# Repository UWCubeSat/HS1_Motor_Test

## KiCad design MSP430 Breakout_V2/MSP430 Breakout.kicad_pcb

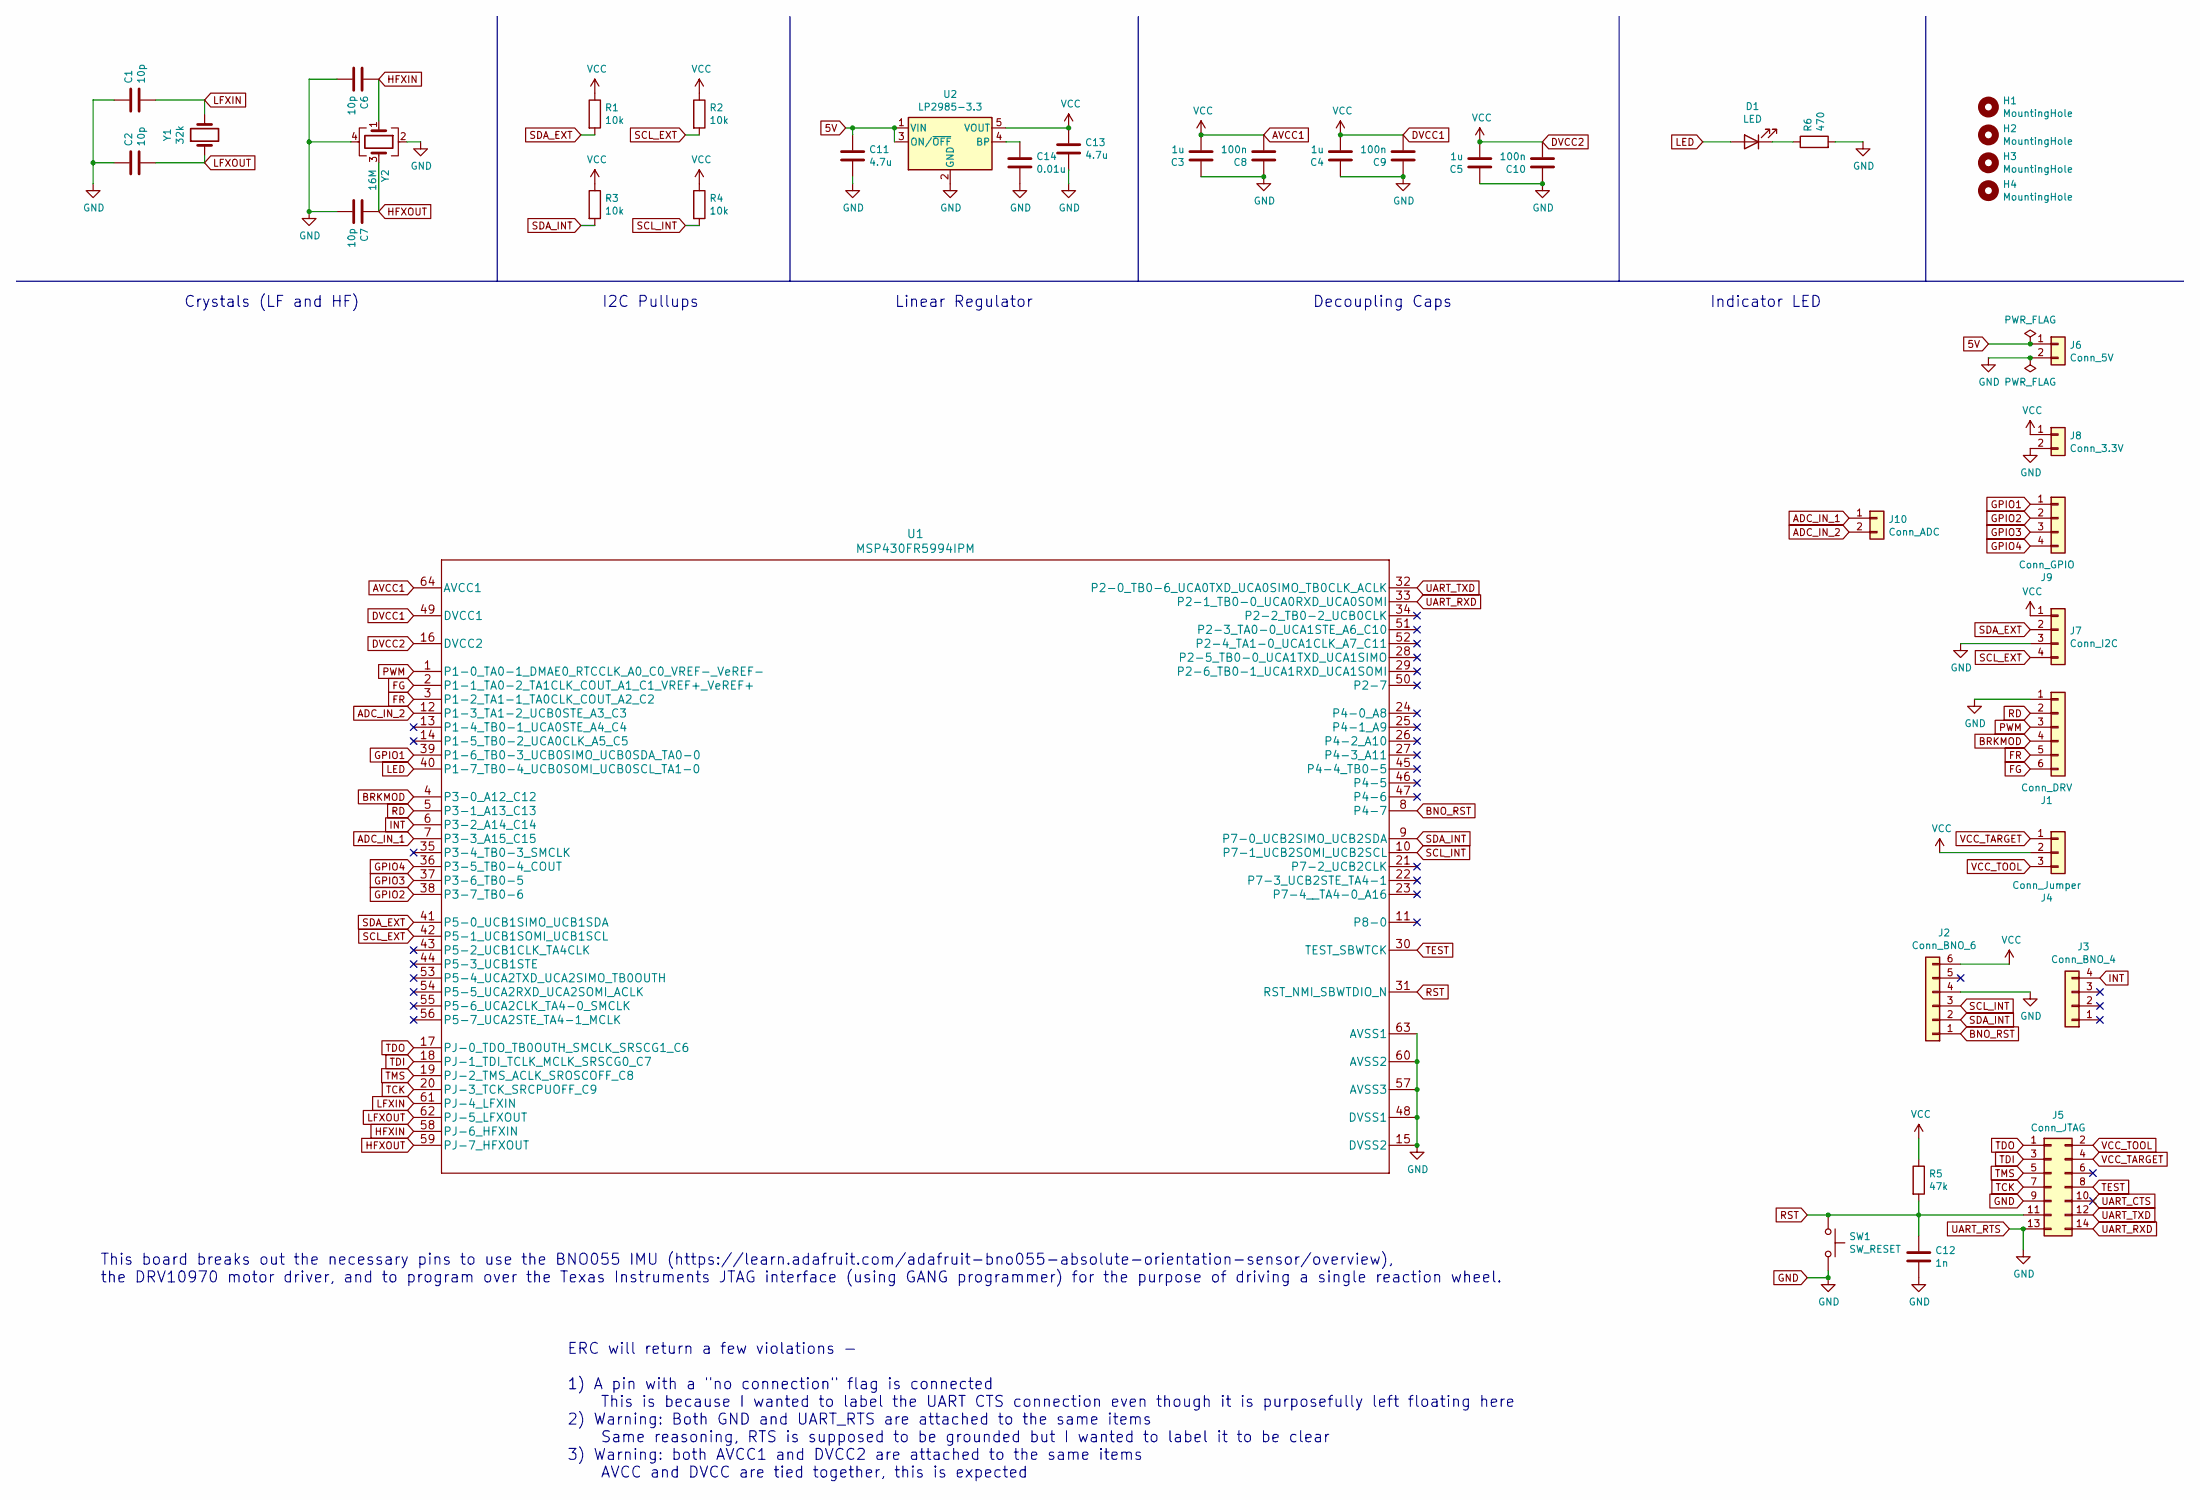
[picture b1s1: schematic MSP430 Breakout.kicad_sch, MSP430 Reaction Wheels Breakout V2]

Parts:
C1, C2, C6, C7: 10p; C_0805_2012Metric_Pad1.18x1.45mm_HandSolder
C3, C4, C5: 1u; C_0805_2012Metric_Pad1.18x1.45mm_HandSolder
C8, C9, C10: 100n; C_0805_2012Metric_Pad1.18x1.45mm_HandSolder
C11, C13: 4.7u; C_0805_2012Metric_Pad1.18x1.45mm_HandSolder
C12: 1n; C_0805_2012Metric_Pad1.18x1.45mm_HandSolder
C14: 0.01u; C_0805_2012Metric_Pad1.18x1.45mm_HandSolder
D1: LED; LED_0805_2012Metric_Pad1.15x1.40mm_HandSolder
H1, H2, H3, H4: MountingHole; MountingHole_2.5mm_Pad_Via
J1: Conn_DRV; PinSocket_1x06_P2.54mm_Vertical
J2: Conn_BNO_6; PinSocket_1x06_P2.54mm_Vertical
J3: Conn_BNO_4; PinSocket_1x04_P2.54mm_Vertical
J4: Conn_Jumper; PinHeader_1x03_P2.54mm_Vertical
J5: Conn_JTAG; PinHeader_2x07_P2.54mm_Vertical
J6: Conn_5V; PinSocket_1x02_P2.54mm_Vertical
J7: Conn_I2C; PinSocket_1x04_P2.54mm_Vertical
J8: Conn_3.3V; PinSocket_1x02_P2.54mm_Vertical
J9: Conn_GPIO; PinSocket_1x04_P2.54mm_Vertical
J10: Conn_ADC; PinSocket_1x02_P2.54mm_Vertical
R1, R2, R3, R4: 10k; R_0805_2012Metric_Pad1.20x1.40mm_HandSolder
R5: 47k; R_0805_2012Metric_Pad1.20x1.40mm_HandSolder
R6: 470; R_0805_2012Metric_Pad1.20x1.40mm_HandSolder
SW1: SW_RESET; SW_PUSH_6mm_H5mm
U1: MSP430FR5994IPM
U2: LP2985-3.3; SOT-23-5
Y1: 32k; Crystal_SMD_2012-2Pin_2.0x1.2mm
Y2: 16M; Crystal_SMD_3225-4Pin_3.2x2.5mm_HandSoldering

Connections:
5V: C11.1, J6.1, U2.1 (VIN), U2.3 (ON/~OFF)
ADC_IN_1: J10.1, U1.7 (P3-3_A15_C15)
ADC_IN_2: J10.2, U1.12 (P1-3_TA1-2_UCB0STE_A3_C3)
AVCC1: C3.2, C4.2, C5.2, C8.2, C9.2, C10.2, C13.1, J2.6, J4.2, J7.1, J8.1, R1.1, R2.1, R3.1, R4.1, R5.1, U1.16 (DVCC2), U1.49 (DVCC1), U1.64 (AVCC1), U2.5 (VOUT)
BNO_RST: J2.1, U1.8 (P4-7)
BRKMOD: J1.4, U1.4 (P3-0_A12_C12)
FG: J1.6, U1.2 (P1-1_TA0-2_TA1CLK_COUT_A1_C1_VREF+_VeRE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)
FR: J1.5, U1.3 (P1-2_TA1-1_TA0CLK_COUT_A2_C2)
GND: C1.1, C2.1, C3.1, C4.1, C5.1, C6.2, C7.2, C8.1, C9.1, C10.1, C11.2, C12.2, C13.2, C14.2, J1.1, J2.4, J5.9, J5.13, J6.2, J7.3, J8.2, R6.2, SW1.2, U1.15 (DVSS2), U1.48 (DVSS1), U1.57 (AVSS3), U1.60 (AVSS2), U1.63 (AVSS1), U2.2 (GND), Y2.2, Y2.4
GPIO1: J9.1, U1.39 (P1-6_TB0-3_UCB0SIMO_UCB0SDA_TA0-0)
GPIO2: J9.2, U1.38 (P3-7_TB0-6)
GPIO3: J9.3, U1.37 (P3-6_TB0-5)
GPIO4: J9.4, U1.36 (P3-5_TB0-4_COUT)
HFXIN: C6.1, U1.58 (PJ-6_HFXIN), Y2.1
HFXOUT: C7.1, U1.59 (PJ-7_HFXOUT), Y2.3
INT: J3.4, U1.6 (P3-2_A14_C14)
LED: D1.2 (A), U1.40 (P1-7_TB0-4_UCB0SOMI_UCB0SCL_TA1-0)
LFXIN: C1.2, U1.61 (PJ-4_LFXIN), Y1.2
LFXOUT: C2.2, U1.62 (PJ-5_LFXOUT), Y1.1
unnamed: C14.1, U2.4 (BP)
unnamed: D1.1 (K), R6.1
PWM: J1.3, U1.1 (P1-0_TA0-1_DMAE0_RTCCLK_A0_C0_VREF-_VeR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)
RD: J1.2, U1.5 (P3-1_A13_C13)
RST: C12.1, J5.11, R5.2, SW1.1, U1.31 (RST_NMI_SBWTDIO_N)
SCL_EXT: J7.4, R2.2, U1.42 (P5-1_UCB1SOMI_UCB1SCL)
SCL_INT: J2.3, R4.2, U1.10 (P7-1_UCB2SOMI_UCB2SCL)
SDA_EXT: J7.2, R1.2, U1.41 (P5-0_UCB1SIMO_UCB1SDA)
SDA_INT: J2.2, R3.2, U1.9 (P7-0_UCB2SIMO_UCB2SDA)
TCK: J5.7, U1.20 (PJ-3_TCK_SRCPUOFF_C9)
TDI: J5.3, U1.18 (PJ-1_TDI_TCLK_MCLK_SRSCG0_C7)
TDO: J5.1, U1.17 (PJ-0_TDO_TB0OUTH_SMCLK_SRSCG1_C6)
TEST: J5.8, U1.30 (TEST_SBWTCK)
TMS: J5.5, U1.19 (PJ-2_TMS_ACLK_SROSCOFF_C8)
UART_CTS: J5.10
UART_RXD: J5.14, U1.33 (P2-1_TB0-0_UCA0RXD_UCA0SOMI)
UART_TXD: J5.12, U1.32 (P2-0_TB0-6_UCA0TXD_UCA0SIMO_TB0CLK_ACLK)
VCC_TARGET: J4.1, J5.4
VCC_TOOL: J4.3, J5.2

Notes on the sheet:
I2C Pullups
This board breaks out the necessary pins to use the BNO055 IMU (https://learn.adafruit.com/adafruit-bno055-absolute-orientation-sensor/overview), the DRV10970 motor driver, and to program over the Texas Instruments JTAG interface (using GANG programmer) for the purpose of driving a single reaction 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
ERC will return a few violations - 1) A pin with a "no connection" flag is connected This is because I wanted to label the UART CTS connection even though it is purposefully left floating here 2) Warning: Both GND and UART_RTS are attached to the same items Same reasoning, RTS is supposed to be gro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
Linear Regulator
Decoupling Caps
Crystals (LF and HF)
Indicator LED

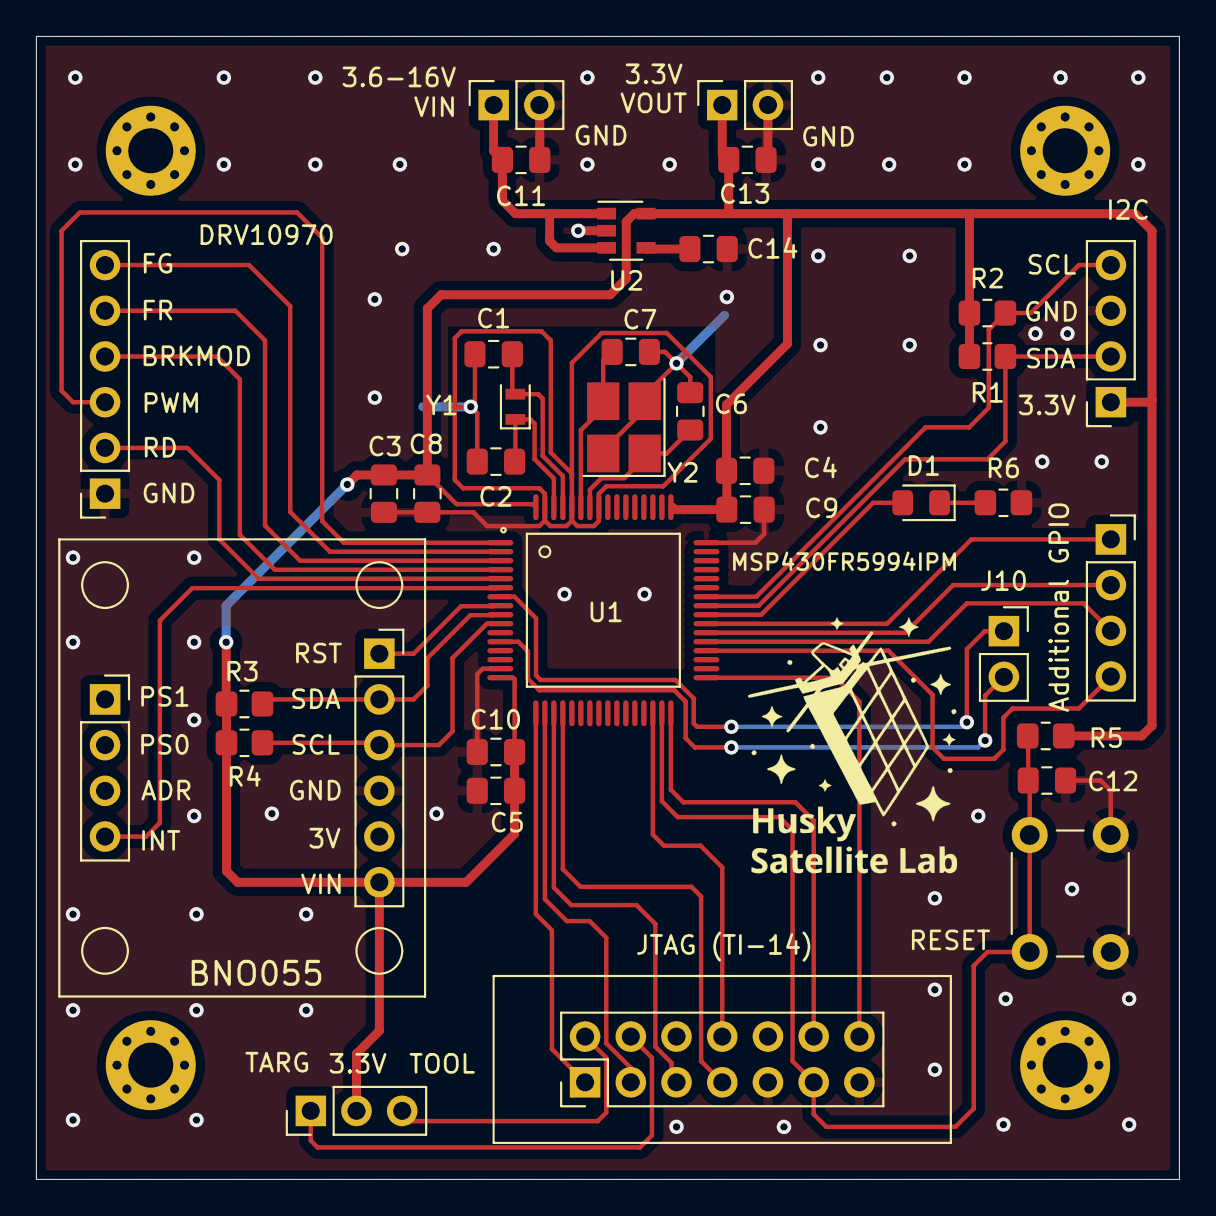
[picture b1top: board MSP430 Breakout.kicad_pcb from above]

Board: 2 copper layers, 63.5 x 63.5 mm, 40 parts (0 on the bottom side), 37 nets.

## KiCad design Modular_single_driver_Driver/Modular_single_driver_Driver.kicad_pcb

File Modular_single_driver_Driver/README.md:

# DRV10970 Driver Board
The DRV10970 Driver Board contains a single Texas Instruments DRV10970 brushless DC motor driver IC. The board exposes all the necessary features for driving a FAULHABER 1509T006B motor.

In the case that a switch is not installed, reference the silkscreened labels inside of the switch footprint when making connections to ensure accurate pin identificaiton. In the default configuration, FR and BRKMOD are pulled low while DAA and CMTMOD are left floating.

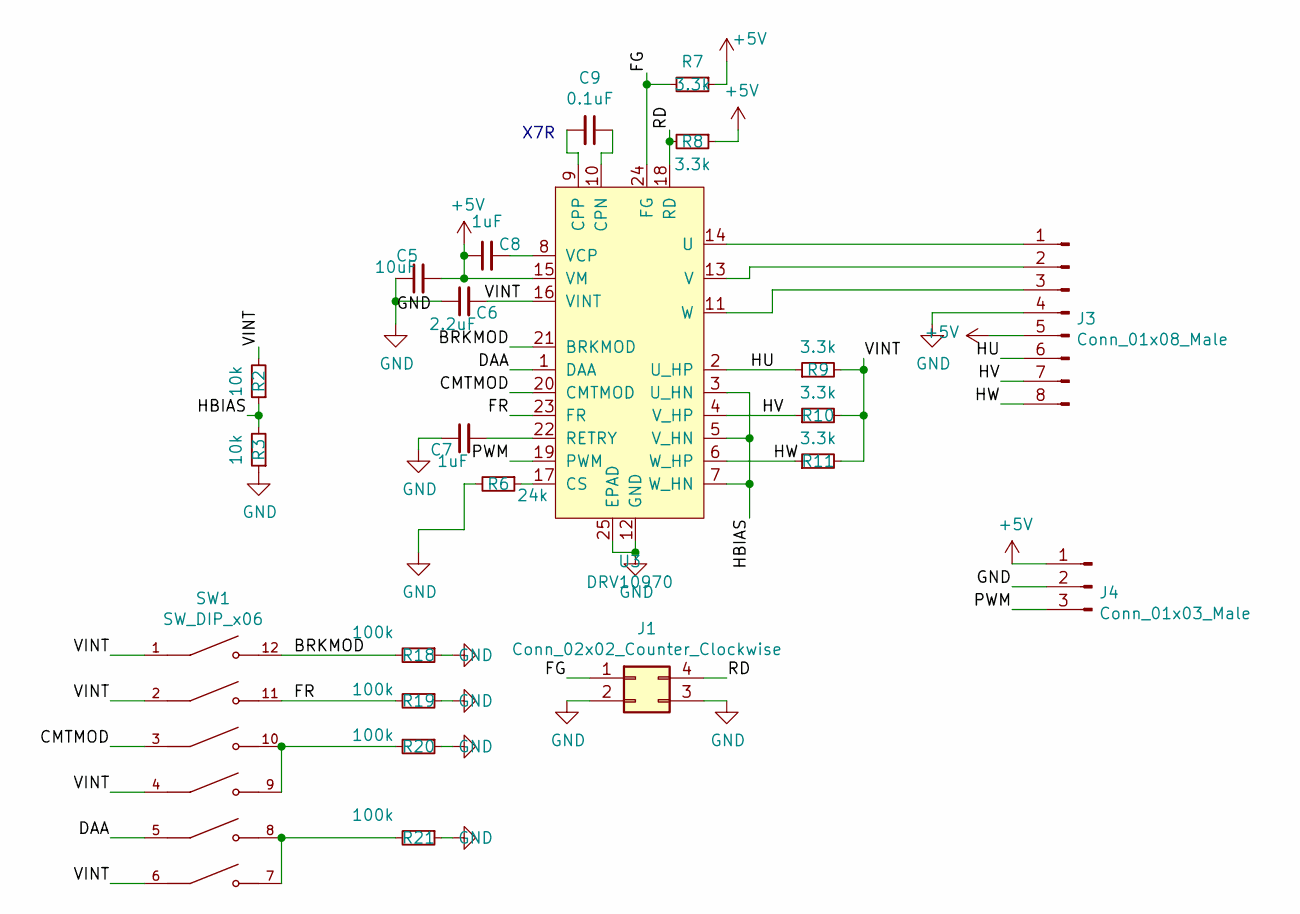
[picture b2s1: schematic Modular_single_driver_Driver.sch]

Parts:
C5: 10uF; C_0603_1608Metric
C6: 2.2uF; C_0603_1608Metric
C7, C8: 1uF; C_0603_1608Metric
C9: 0.1uF; C_0603_1608Metric
J1: Conn_02x02_Counter_Clockwise; PinHeader_2x02_P2.54mm_Vertical
J3: Conn_01x08_Male; PinHeader_1x08_P2.54mm_Vertical
J4: Conn_01x03_Male; PinHeader_1x03_P2.54mm_Vertical
R2, R3: 10k; R_0603_1608Metric
R6: 24k; R_0603_1608Metric
R7, R8, R9, R10, R11: 3.3k; R_0603_1608Metric
R18, R19, R20, R21: 100k; R_0603_1608Metric
SW1: SW_DIP_x06; DIP762W56P254L1772H585Q12
U3: DRV10970; HTSSOP-24-1EP_4.4x7.8mm_P0.65mm_EP3.4x7.8mm_Mask2.4x4.68mm_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

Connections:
+5V: C5.2, C8.1, J3.5, J4.1, R7.1, R8.1, U3.15 (VM); also elsewhere on the board
/BRKMOD: R18.2, SW1.12, U3.21 (BRKMOD)
/CMTMOD: SW1.3, U3.20 (CMTMOD)
/DAA: SW1.5, U3.1 (DAA)
/FG: J1.1, R7.2, U3.24 (FG)
/FR: R19.2, SW1.11, U3.23 (FR)
/HBIAS: R2.1, R3.2, U3.3 (U_HN), U3.5 (V_HN), U3.7 (W_HN)
/HU: J3.6, R9.1, U3.2 (U_HP)
/HV: J3.7, R10.1, U3.4 (V_HP)
/HW: J3.8, R11.1, U3.6 (W_HP)
/PWM: J4.3, U3.19 (PWM); also elsewhere on the board
/RD: J1.4, R8.2, U3.18 (RD)
/VINT: C6.2, R2.2, R9.2, R10.2, R11.2, SW1.1, SW1.2, SW1.4, SW1.6, U3.16 (VINT)
GND: C5.1, C6.1, C7.1, J1.2, J1.3, J3.4, J4.2, R3.1, R6.2, R18.1, R19.1, R20.1, R21.1, U3.12 (GND), U3.25 (EPAD); also elsewhere on the board
unnamed: C7.2, U3.22 (RETRY)
unnamed: C8.2, U3.8 (VCP)
unnamed: C9.1, U3.10 (CPN)
unnamed: C9.2, U3.9 (CPP)
unnamed: J3.1, U3.14 (U)
unnamed: J3.2, U3.13 (V)
unnamed: J3.3, U3.11 (W)
unnamed: R6.1, U3.17 (CS)
unnamed: R20.2, SW1.9, SW1.10
unnamed: R21.2, SW1.7, SW1.8

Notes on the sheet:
X7R

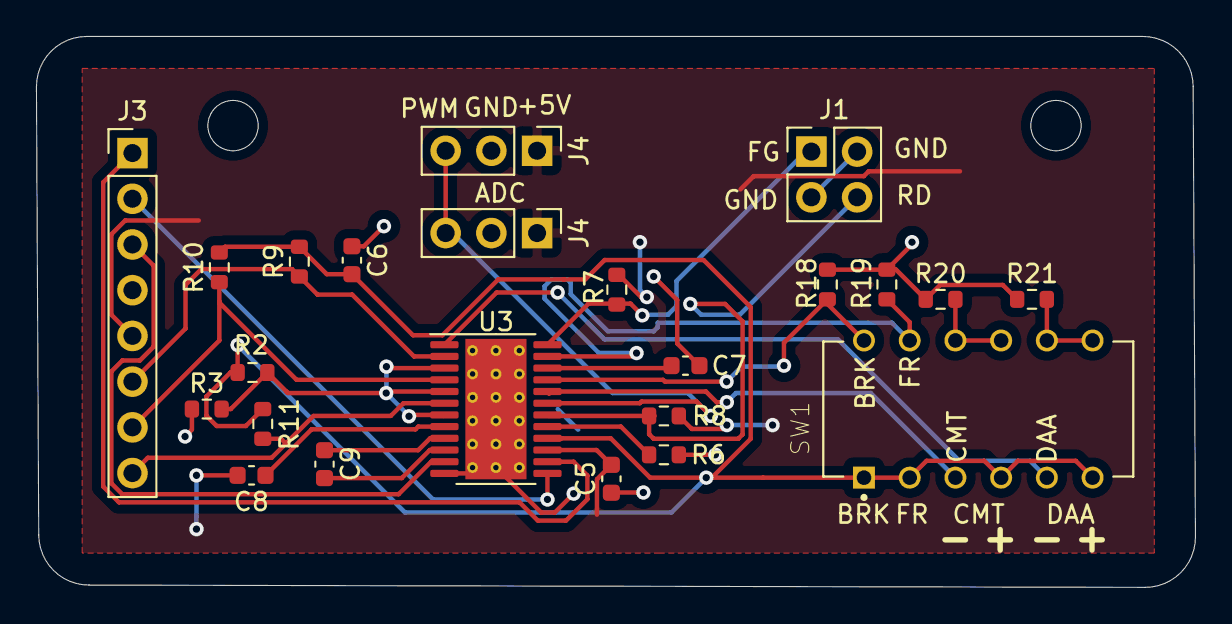
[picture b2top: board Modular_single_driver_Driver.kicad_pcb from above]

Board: 2 copper layers, 64.4 x 30.6 mm, 23 parts (0 on the bottom side), 24 nets.

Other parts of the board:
J4#2: Conn_01x03_Male; PinHeader_1x03_P2.54mm_Vertical

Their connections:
+5V: J4#2.1; also elsewhere on the board
/PWM: J4#2.3; also elsewhere on the board
GND: J4#2.2; also elsewhere on the board

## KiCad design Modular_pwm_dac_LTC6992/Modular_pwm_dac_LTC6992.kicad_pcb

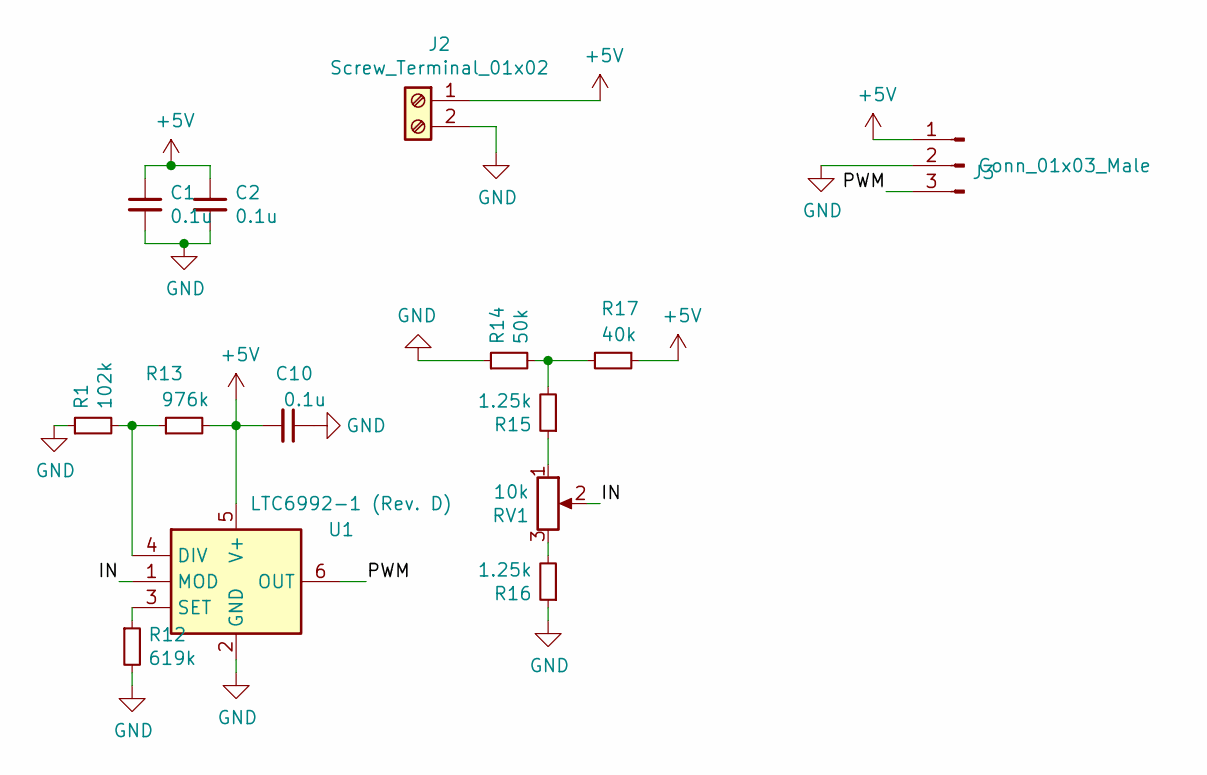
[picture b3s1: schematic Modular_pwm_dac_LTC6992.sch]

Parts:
C1, C2, C10: 0.1u; C_0603_1608Metric
J2: Screw_Terminal_01x02; TerminalBlock_Phoenix_PT-1,5-2-3.5-H_1x02_P3.50mm_Horizontal
J3: Conn_01x03_Male; PinHeader_1x03_P2.54mm_Vertical
R1: 102k; R_0603_1608Metric
R12: 619k; R_0603_1608Metric
R13: 976k; R_0603_1608Metric
R14: 50k; R_0603_1608Metric
R15, R16: 1.25k; R_0603_1608Metric
R17: 40k; R_0603_1608Metric
RV1: 10k; PinHeader_1x03_P2.54mm_Vertical
U1: LTC6992-1 (Rev. D); SOT-23-6_Handsoldering

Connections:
+5V: C1.1, C2.1, C10.2, J2.1, J3.1, R13.2, R17.1, U1.5 (V+); also elsewhere on the board
/IN: RV1.2, U1.1 (MOD)
/PWM: J3.3, U1.6 (OUT); also elsewhere on the board
GND: C1.2, C2.2, C10.1, J2.2, J3.2, R1.1, R12.2, R14.1, R16.1, U1.2 (GND); also elsewhere on the board
unnamed: R1.2, R13.1, U1.4 (DIV)
unnamed: R12.1, U1.3 (SET)
unnamed: R14.2, R15.2, R17.2
unnamed: R15.1, RV1.1
unnamed: R16.2, RV1.3

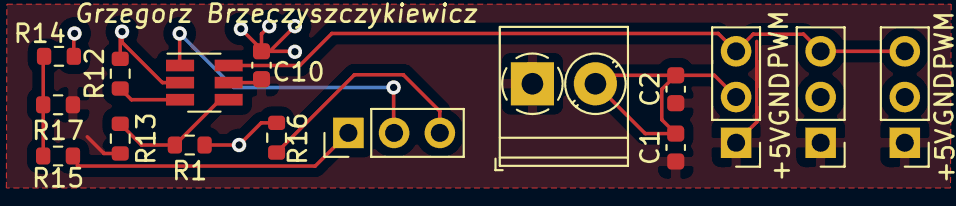
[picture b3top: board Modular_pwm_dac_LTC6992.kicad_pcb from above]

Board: 2 copper layers, 16 parts (0 on the bottom side), 9 nets.

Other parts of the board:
J3#2, J3#3: Conn_01x03_Male; PinHeader_1x03_P2.54mm_Vertical

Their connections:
+5V: J3#2.1, J3#3.1; also elsewhere on the board
/PWM: J3#2.3, J3#3.3; also elsewhere on the board
GND: J3#2.2, J3#3.2; also elsewhere on the board

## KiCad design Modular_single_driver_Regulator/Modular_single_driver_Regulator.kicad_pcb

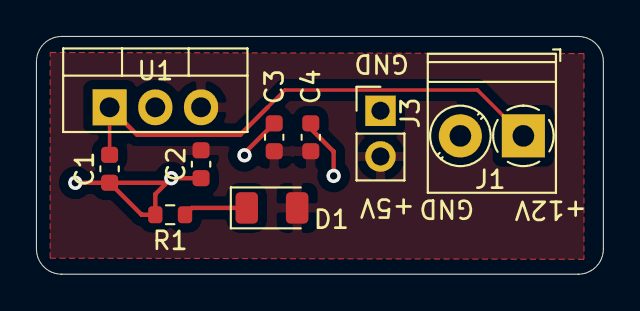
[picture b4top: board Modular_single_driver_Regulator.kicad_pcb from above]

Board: 2 copper layers, 31.5 x 13.2 mm, 9 parts (0 on the bottom side), 4 nets.

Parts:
C1: 0.33u; C_0603_1608Metric
C2, C3, C4: 0.1u; C_0603_1608Metric
D1: LED; LED_1206_3216Metric
J1: Screw_Terminal_01x02; TerminalBlock_Phoenix_PT-1,5-2-3.5-H_1x02_P3.50mm_Horizontal
J3: Conn_01x02_Male; PinHeader_1x02_P2.54mm_Vertical
R1: 510; R_0603_1608Metric
U1: LM7805_TO220; TO-220-3_Vertical

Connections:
+5V: C2.1, C3.1, C4.1, D1.2, J3.2, U1.3
+12V: C1.1, J1.1, U1.1
GND: C1.2, C2.2, C3.2, C4.2, J1.2, J3.1, R1.2, U1.2
unnamed: D1.1, R1.1

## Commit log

2020-11-28 Added design files
2020-12-04 Started circuit for 555 timer duty cycle
    PWM Duty Cycle signal generator for reaction wheel testing
2020-12-06 Organizing
2020-12-06 Organization
2020-12-06 New RW driver PCB
    Instead of AVR, using analog to PWM duty cycle converter IC
2020-12-06 slight adjustments to new rw pcb
2020-12-06 Added header for lock and tach
2020-12-15 Added DIP switch
    DIP switch will control various aspects of the control algorithm
2020-12-15 Slight changes
2020-12-15 Started PCB
2020-12-21 Changed current sensing resistor
2020-12-21 More PCB work
2021-01-06 Basically finished pcb
2021-01-06 Finished...?
2021-01-11 Starting Rev. 2
2021-01-12 Moved stuff around
2021-01-12 Created Rev.2 for test
2021-01-13 Created new project for PWM test
2021-01-13 More PWM dac stuffff
2021-01-13 njoi
2021-01-14 Mostly finished PCB for ADC
2021-01-14 Finished PCB with header output/support
2021-01-14 stuff
2021-01-14 Built PCB
2021-01-18 Attempted to LTspice
2021-01-19 Organized and renamed files
2021-01-26 Finished All
2021-01-27 More
2021-01-27 some stuyff
2021-02-01 I guess i did some stuff
2021-02-01 Yes they are
2021-02-15 Basically finished MSP430 Single
2021-04-08 NEW PCB
    Changed some names of old PCBs, and created new PCB with the new package
2021-04-14 Built a matlab script, terrible scripts
    Built scripts for 555 timer for turning a potentiometer (i.e. knob) to adjust pwm signal dooty cycle
2021-07-25 MSP430 Breakout Board
    Board for interfacing BNO055 IMU and DRV10970 motor driver with MSP430FR5994IPM
2021-11-17 Updated connections and component values
    - Updated component values to reflect those shown in the datasheet
    - Connected HBIAS pins to each other
    - Connected PowerPAD to ground plane
    - Cleaned up traces
    - Added some silkscreen labels to facilitate testing
2022-01-22 Added README.md
2022-03-03 Add V2 MSP430 board design
    V2 fixes:
    Hand solder footprint for high frequency crystal
    BSL UART pins fixed (tx and rx were backward on V1)
    Added pins to access ADC inputs, for using a potentiometer to control motor speed.
